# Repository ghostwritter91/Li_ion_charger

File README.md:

1. Li-ion battery charger (mainly 18V) based on MAX745. 
2. PCB design for homemade production. 
3. KiCAD project.

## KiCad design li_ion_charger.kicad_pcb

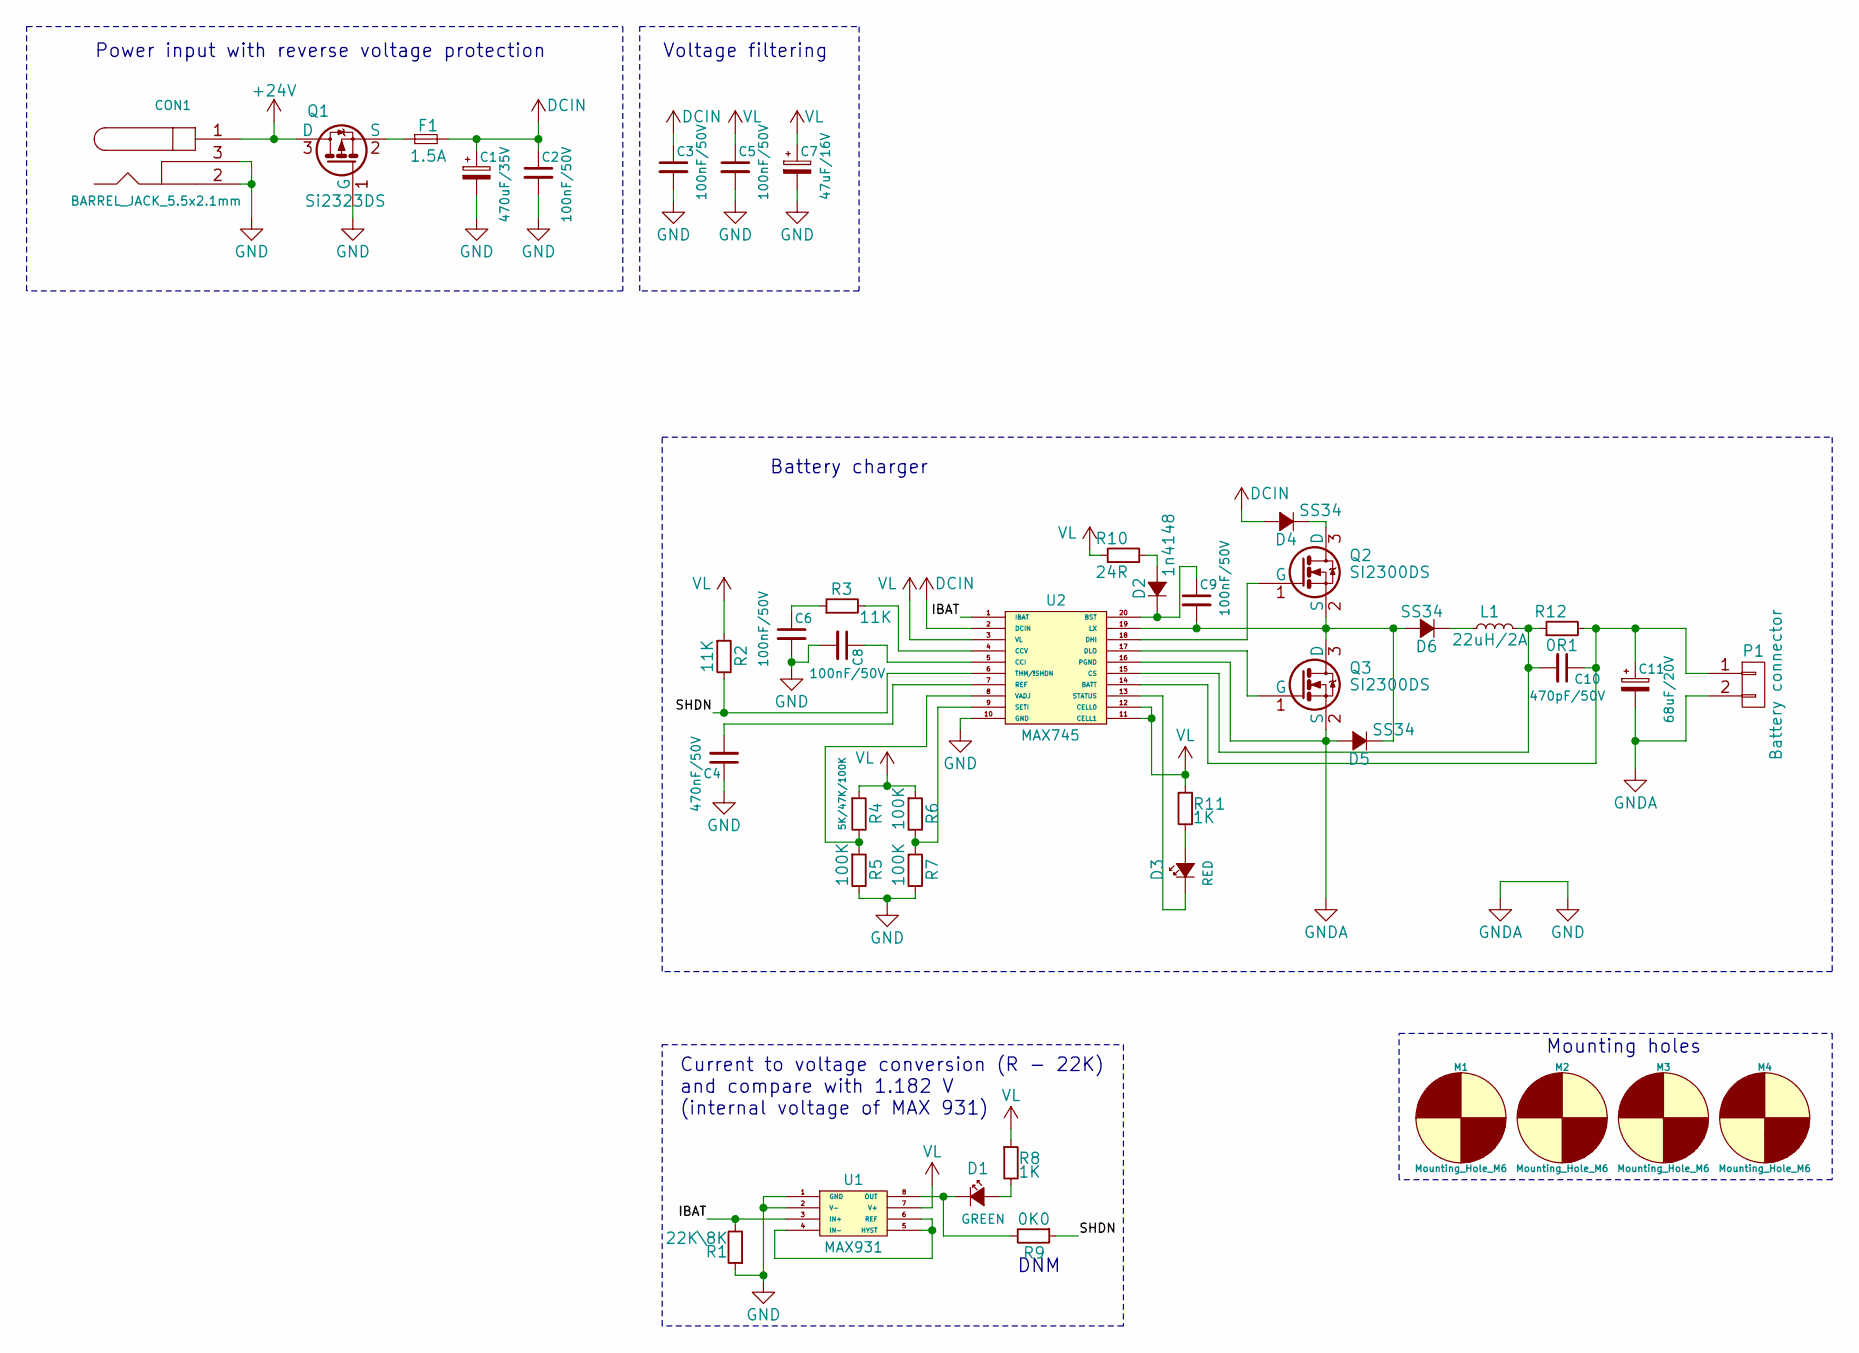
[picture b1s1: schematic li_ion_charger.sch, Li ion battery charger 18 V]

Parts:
C1: 470uF/35V; C_Radial_D10_L16_P5
C2, C3, C5, C6, C8, C9: 100nF/50V; C_0805_HandSoldering
C4: 470nF/50V; C_0805_HandSoldering
C7: 47uF/16V; c_elec_5x5.7
C10: 470pF/50V; C_0805_HandSoldering
C11: 68uF/20V; TantalC_SizeV_EIA-7343
CON1: BARREL_JACK_5.5x2.1mm; JACK_DC
D1: GREEN; LED-3MM
D2: 1n4148; Diode_DO-35_SOD27_Horizontal_RM10
D3: RED; LED-3MM
D4, D5, D6: SS34; DO-214AC
F1: 1.5A; Fuse5x20mm
L1: 22uH/2A; DR125
M1, M2, M3, M4: Mounting_Hole_M6; MountingHole_6.4mm_M6_reduced
P1: Battery connector; Pin_Header_Straight_1x02
Q1: Si2323DS; SOT-23
Q2, Q3: SI2300DS; SOT-23
R1: 22K\\8K; R_0805_HandSoldering
R2, R3: 11K; R_0805_HandSoldering
R4: 5K/47K/100K; R_0805_HandSoldering
R5, R6, R7: 100K; R_0805_HandSoldering
R8, R11: 1K; R_0805_HandSoldering
R9: 0K0; R_0805_HandSoldering
R10: 24R; R_0805_HandSoldering
R12: 0R1; R_0805_HandSoldering
U1: MAX931; SO8
U2: MAX745; SSOP-20_5.3x7.2mm_Pitch0.65mm

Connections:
+24V: CON1.1, Q1.3 (D)
/IBAT: R1.2, U1.3 (IN+), U2.1 (IBAT)
/SHDN: R2.2, R9.1, U2.6 (THM/!SHDN)
DCIN: C1.1, C2.1, C3.1, D4.2 (A), F1.2, U2.2 (DCIN)
GND: C1.2, C2.2, C3.2, C4.1, C5.2, C6.2, C7.2, C8.2, C11.2, CON1.2, CON1.3, D5.2 (A), P1.2, Q1.1 (G), Q3.2 (S), R1.1, R5.2, R7.2, U1.1 (GND), U1.2 (V-), U2.10 (GND), U2.16 (PGND)
unnamed: C4.2, U2.7 (REF)
unnamed: C6.1, R3.1
unnamed: C8.1, U2.5 (CCI)
unnamed: C9.1, D2.1 (K), U2.20 (BST)
unnamed: C9.2, D5.1 (K), D6.2 (A), Q2.2 (S), Q3.3 (D), U2.19 (LX)
unnamed: C10.1, C11.1, P1.1, R12.2, U2.14 (BATT)
unnamed: C10.2, L1.2, R12.1, U2.15 (CS)
unnamed: D1.1 (K), R9.2, U1.8 (OUT)
unnamed: D1.2 (A), R8.2
unnamed: D2.2 (A), R10.2
unnamed: D3.1 (K), U2.13 (STATUS)
unnamed: D3.2 (A), R11.2
unnamed: D4.1 (K), Q2.3 (D)
unnamed: D6.1 (K), L1.1
unnamed: F1.1, Q1.2 (S)
unnamed: Q2.1 (G), U2.18 (DHI)
unnamed: Q3.1 (G), U2.17 (DLO)
unnamed: R3.2, U2.4 (CCV)
unnamed: R4.2, R5.1, U2.8 (VADJ)
unnamed: R6.2, R7.1, U2.9 (SETI)
unnamed: U1.4 (IN-), U1.5 (HYST), U1.6 (REF)
VL: C5.1, C7.1, R2.1, R4.1, R6.1, R8.1, R10.1, R11.1, U1.7 (V+), U2.3 (VL), U2.11 (CELL1), U2.12 (CELL0)

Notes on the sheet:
Power input with reverse voltage protection
Current to voltage conversion (R - 22K) and compare with 1.182 V (internal voltage of MAX 931)
Voltage filtering
Battery charger
Mounting holes
DNM

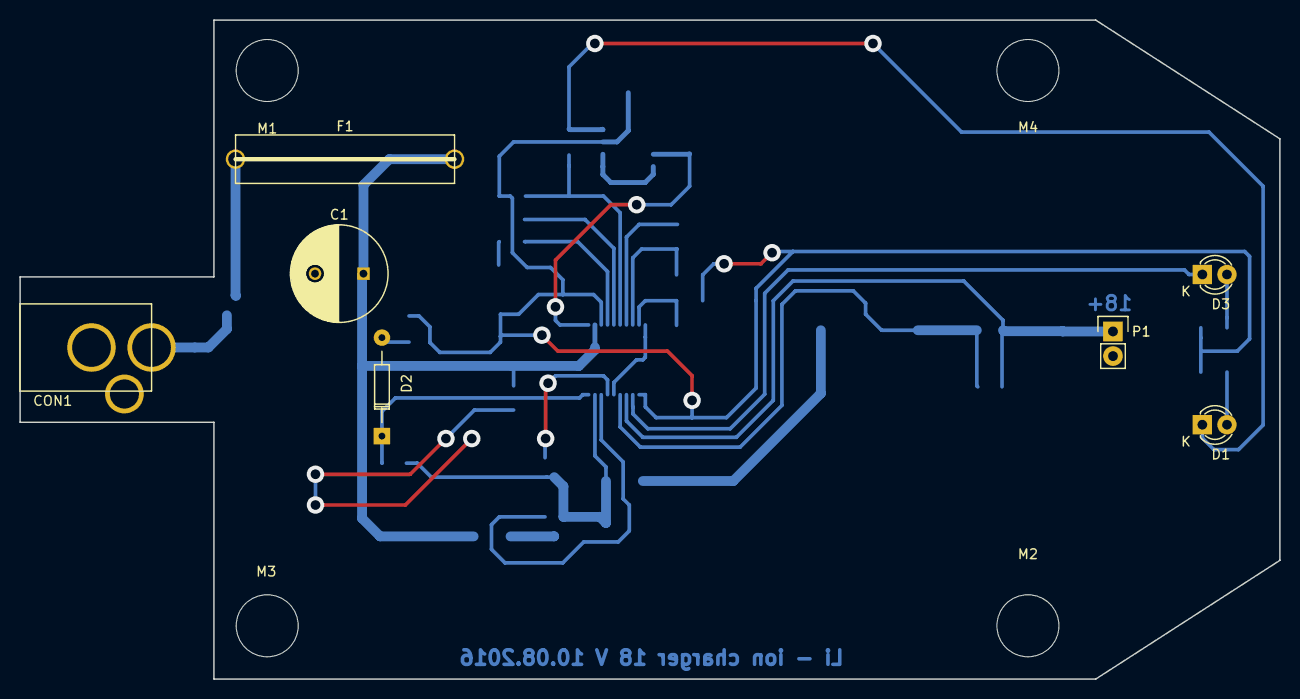
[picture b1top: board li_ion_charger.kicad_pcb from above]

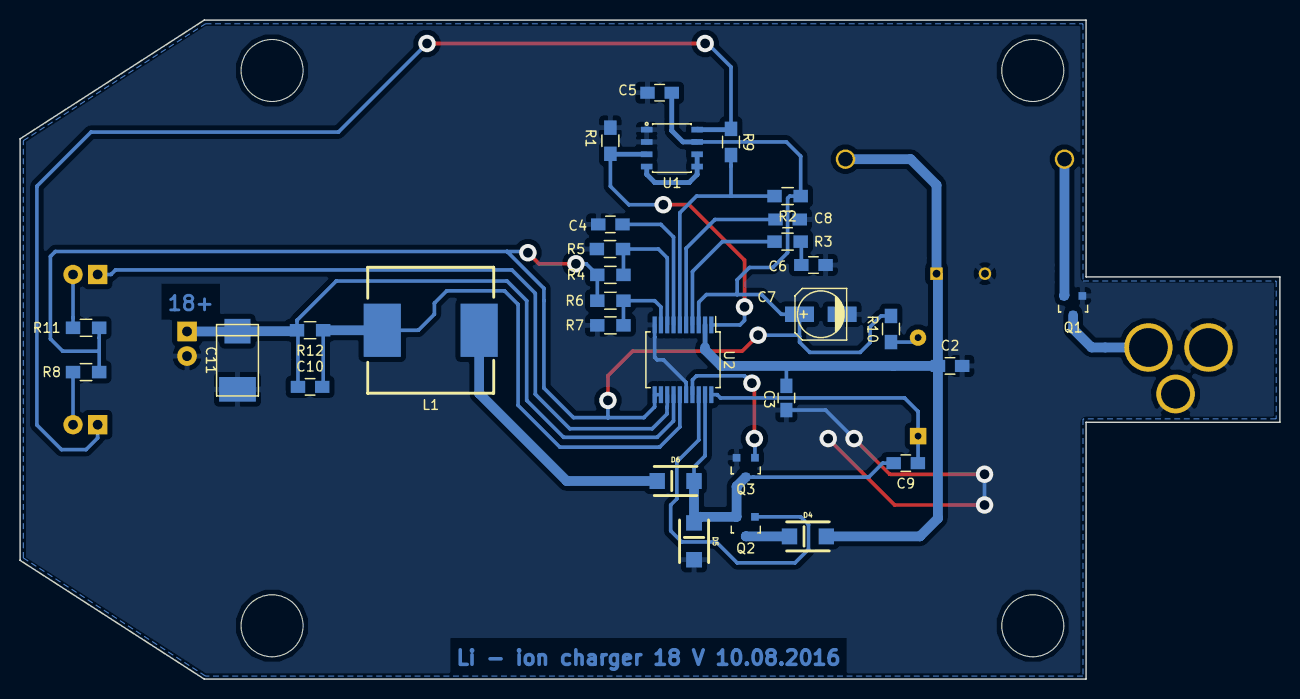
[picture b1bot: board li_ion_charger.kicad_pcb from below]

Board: 2 copper layers, 130.0 x 68.0 mm, 42 parts (31 on the bottom side), 27 nets.

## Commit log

2017-10-31 Init commit
